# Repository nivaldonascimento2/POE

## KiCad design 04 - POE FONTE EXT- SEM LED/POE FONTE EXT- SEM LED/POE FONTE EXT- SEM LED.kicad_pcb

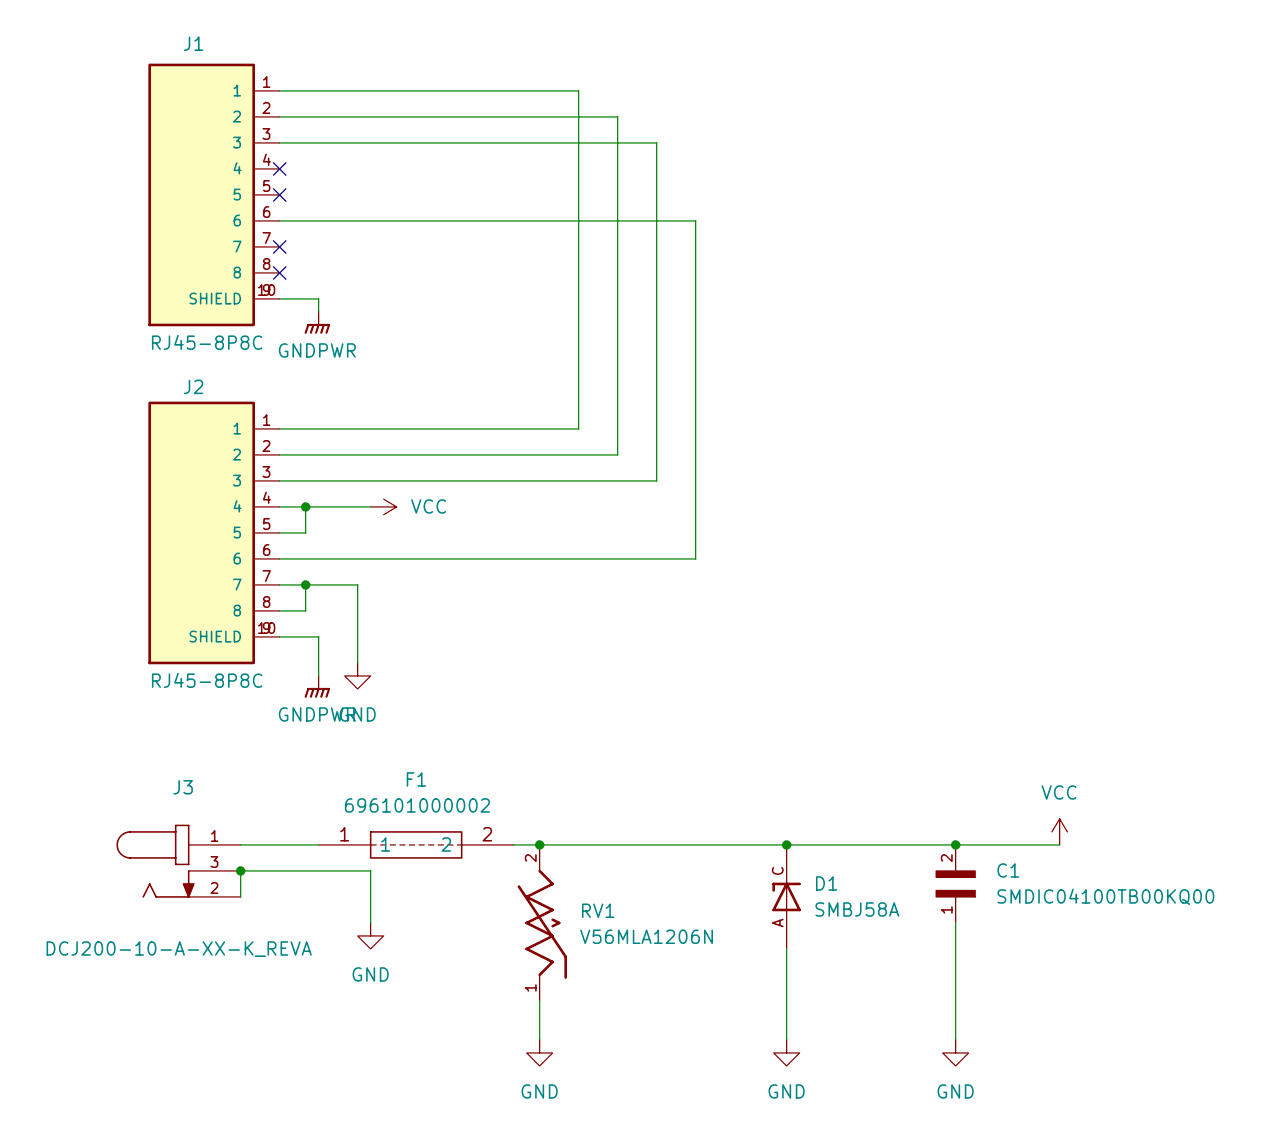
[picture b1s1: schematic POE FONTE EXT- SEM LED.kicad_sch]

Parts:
C1: SMDIC04100TB00KQ00; CAP_SMDIC04100TB00KQ00; PARTREV 04.23
D1: SMBJ58A; DIOM4336X265N; PARTREV F2102
F1: 696101000002; Mouser Part Number 710-696101000002
J1, J2: RJ45-8P8C
J3: DCJ200-10-A-XX-K_REVA; GCT_DCJ200-10-A-XX-K_REVA; PARTREV A
RV1: V56MLA1206N; VARC3216X180N

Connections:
GND: C1.1, D1.A, J2.7, J2.8, J3.2, J3.3, RV1.1
GNDPWR: J1.9 (SHIELD), J1.10 (SHIELD), J2.9 (SHIELD), J2.10 (SHIELD)
unnamed: F1.1, J3.1
unnamed: J1.1, J2.1
unnamed: J1.2, J2.2
unnamed: J1.3, J2.3
unnamed: J1.6, J2.6
VCC: C1.2, D1.C, F1.2, J2.4, J2.5, RV1.2

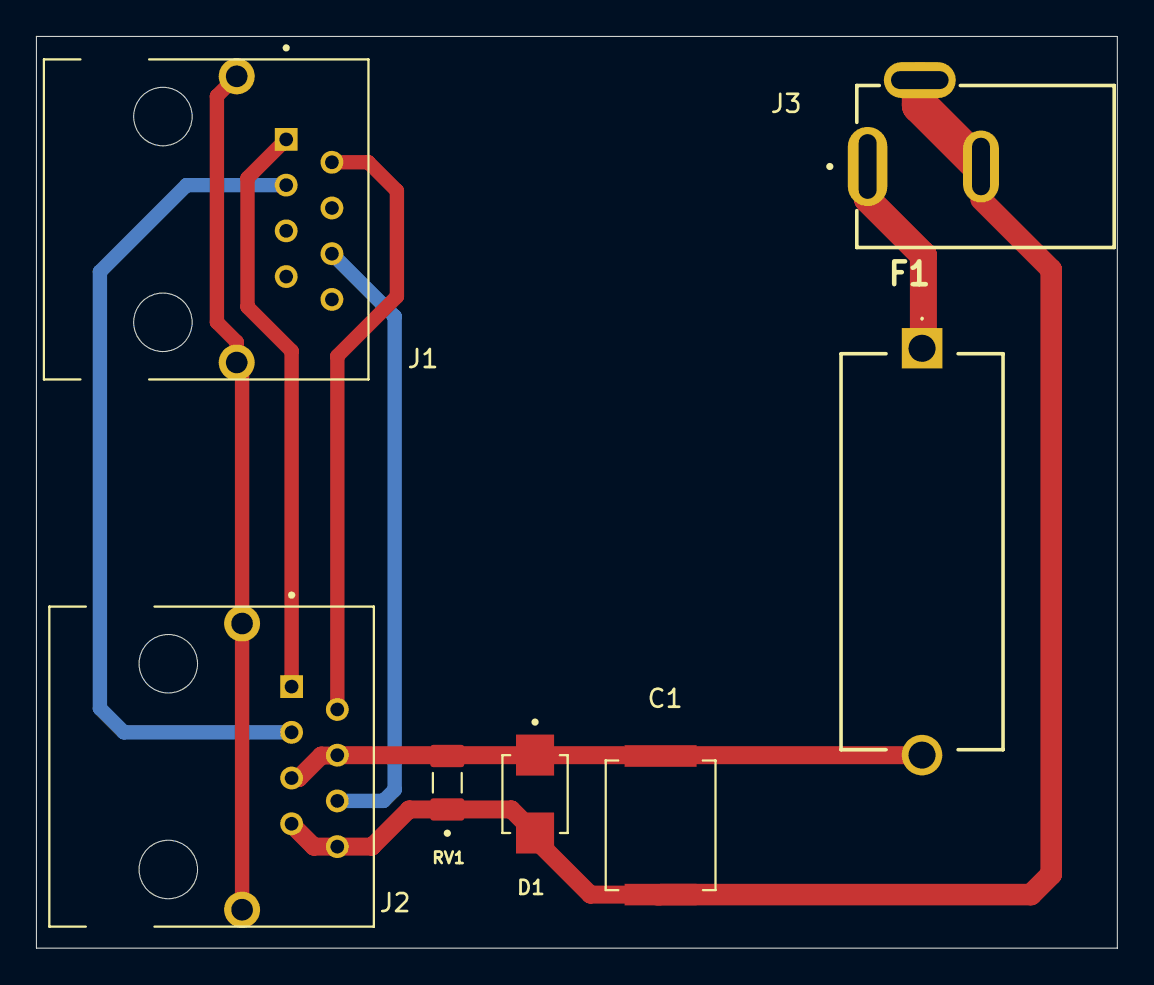
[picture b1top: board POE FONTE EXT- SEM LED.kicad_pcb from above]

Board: 2 copper layers, 60.0 x 50.6 mm, 7 parts (0 on the bottom side), 8 nets.

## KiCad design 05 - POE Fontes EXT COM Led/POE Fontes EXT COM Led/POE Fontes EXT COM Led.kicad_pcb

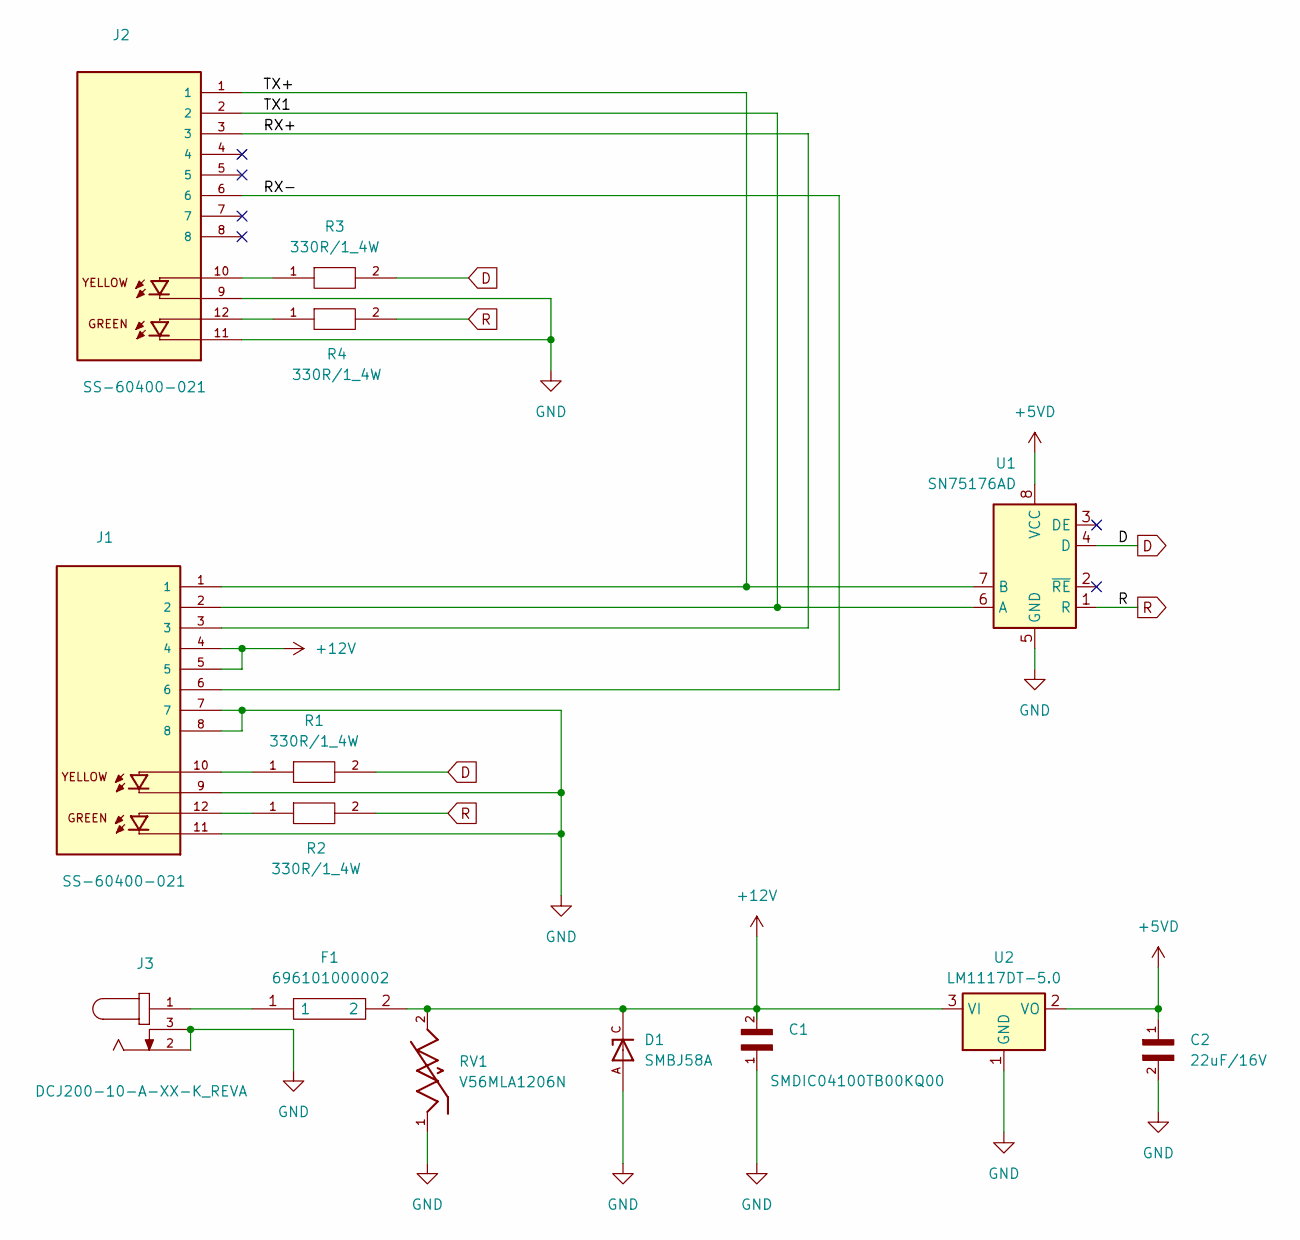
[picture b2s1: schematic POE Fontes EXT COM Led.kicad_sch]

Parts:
C1: SMDIC04100TB00KQ00; CAP_SMDIC04100TB00KQ00; PARTREV 04.23
C2: 22uF/16V; 22uF_16V
D1: SMBJ58A; DIOM4336X265N; PARTREV F2102
F1: 696101000002; Mouser Part Number 710-696101000002
J1, J2: SS-60400-021; BEL_SS-60400-021; PARTREV A0
J3: DCJ200-10-A-XX-K_REVA; GCT_DCJ200-10-A-XX-K_REVA; PARTREV A
R1, R2, R3, R4: 330R/1_4W; RESC2012X65N
RV1: V56MLA1206N; VARC3216X180N
U1: SN75176AD; SOIC-8_3.9x4.9mm_P1.27mm
U2: LM1117DT-5.0; TO-252-3_TabPin2

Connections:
+5VD: C2.1, U1.8 (VCC), U2.2 (VO)
+12V: C1.2, D1.C, F1.2, J1.4, J1.5, RV1.2, U2.3 (VI)
/RX+: J1.3, J2.3
/RX-: J1.6, J2.6
/TX1: J1.2, J2.2, U1.6 (A)
/TX+: J1.1, J2.1, U1.7 (B)
D: R1.2, R3.2, U1.4 (D)
GND: C1.1, C2.2, D1.A, J1.7, J1.8, J1.9, J1.11, J2.9, J2.11, J3.2, J3.3, RV1.1, U1.5 (GND), U2.1 (GND)
unnamed: F1.1, J3.1
unnamed: J1.10, R1.1
unnamed: J1.12, R2.1
unnamed: J2.10, R3.1
unnamed: J2.12, R4.1
R: R2.2, R4.2, U1.1 (R)

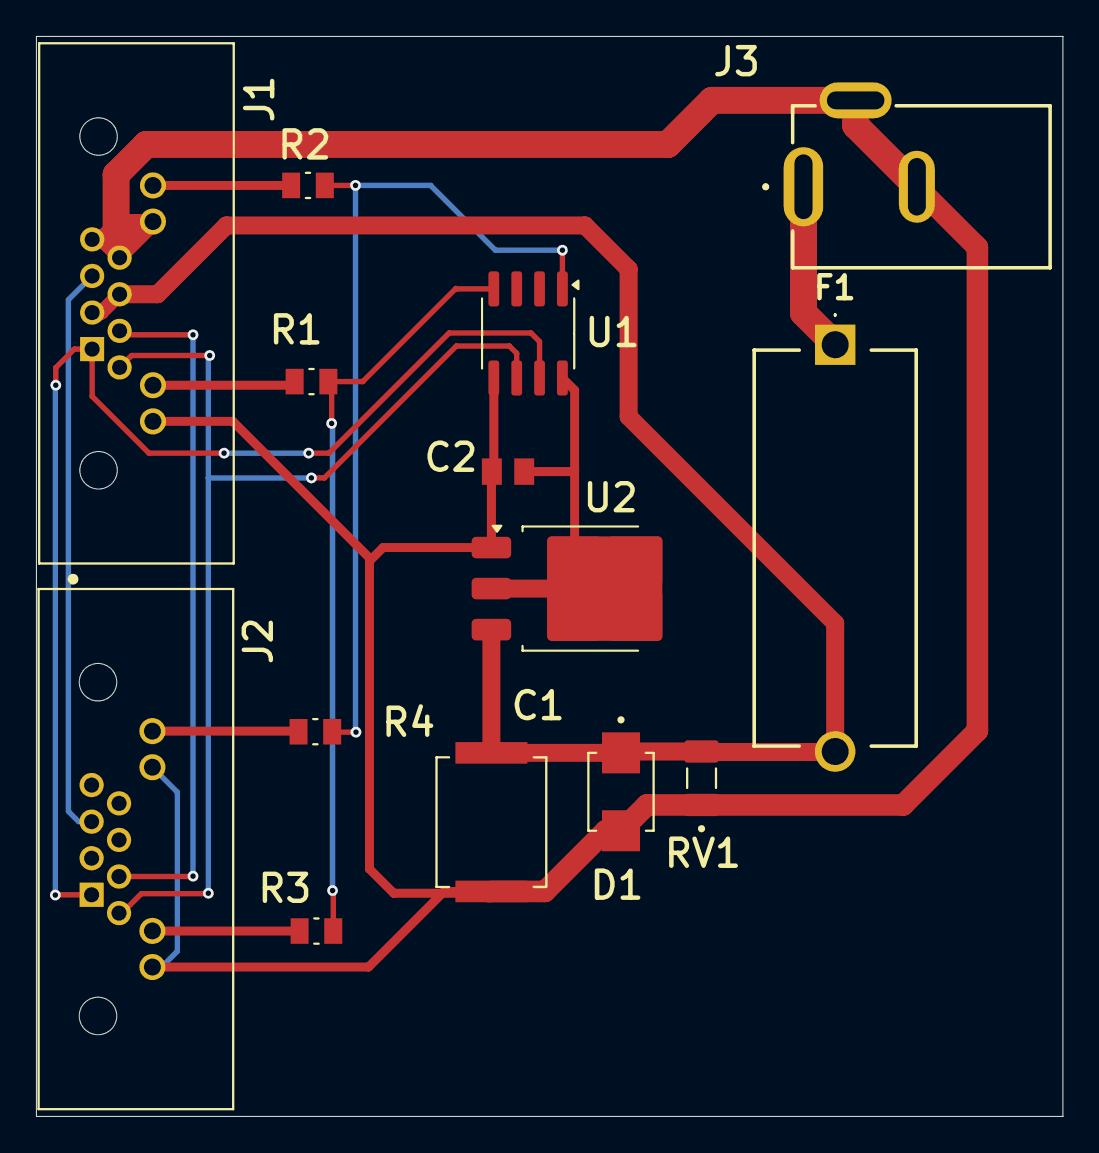
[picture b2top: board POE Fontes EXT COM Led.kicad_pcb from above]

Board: 2 copper layers, 57.0 x 60.0 mm, 14 parts (0 on the bottom side), 14 nets.

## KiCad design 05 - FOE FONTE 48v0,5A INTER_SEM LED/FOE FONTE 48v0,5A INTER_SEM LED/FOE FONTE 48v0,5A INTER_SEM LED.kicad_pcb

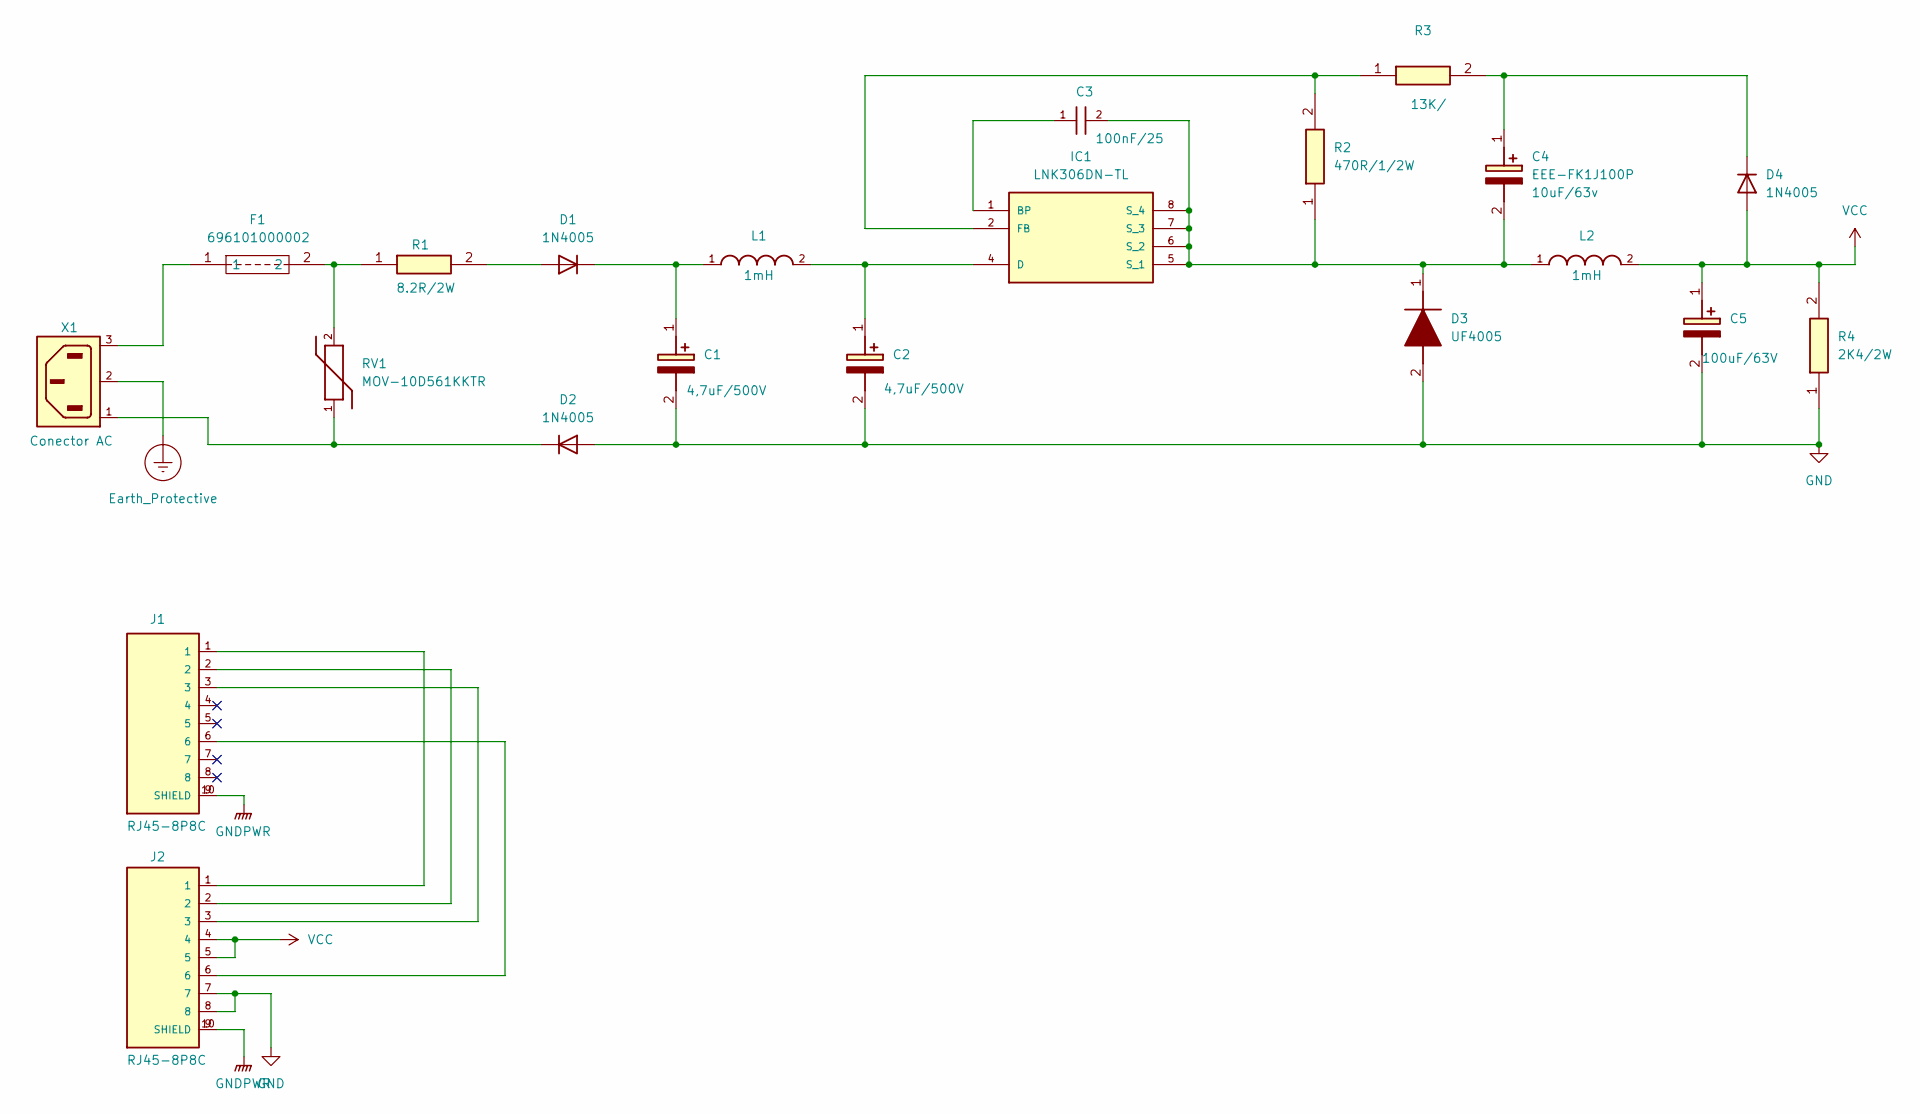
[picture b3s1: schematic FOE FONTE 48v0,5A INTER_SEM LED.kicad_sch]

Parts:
C1, C2: ULT2H4R7MNL1GS; CAPAE1030X1450N; Mouser Part Number 647-ULT2H4R7MNL1GS
C3: 100nF/25; WCAP-CSGP_0603_W
C4: EEE-FK1J100P; EEE1AA101SP; Mouser Part Number 667-EEE-FK1J100P
C5: MAL215097803E3; CAPAE1050X1430N; Mouser Part Number 594-MAL215097803E3
D1, D2, D4: 1N4005; D_DO-41_SOD81_P10.16mm_Horizontal
D3: UF4005; DIOAD1510W84L490D255; Mouser Part Number 637-UF4005
F1: 696101000002; Mouser Part Number 710-696101000002
IC1: LNK306DN-TL; SOIC127P600X175-7N; MOUSER_PART_NUMBER 869-LNK306DN-TL
J1, J2: RJ45-8P8C
L1, L2: WE-PD2HV_1054
R1: CRGH2512J8R2; RESC6432X65N; Mouser Part Number 279-CRGH2512J8R2
R2: RCC1206470RFKEA; RCC1206_e3; Mouser Part Number 71-RCC1206470RFKEA
R3: ERA-6ARB133V; ERA6AEB1020V; Mouser Part Number 667-ERA-6ARB133V
R4: 2K4/2W; RESC6432X65N; Mouser Part Number 279-35212K4FT
RV1: MOV-10D561KKTR; MOV10D511K; MOUSER_PART_NUMBER 652-MOV-10D511K
X1: Conector AC; 6ESRM-P; MPN 6ESRM-P

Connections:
Earth_Protective: X1.2
GND: C1.2 (-), C2.2 (-), C5.2 (-), D2.2 (A), D3.2 (A), J2.7, J2.8, R4.1
GNDPWR: J1.9 (SHIELD), J1.10 (SHIELD), J2.9 (SHIELD), J2.10 (SHIELD)
unnamed: C1.1 (+), D1.1 (K), L1.1
unnamed: C2.1 (+), IC1.4 (D), L1.2
unnamed: C4.1 (+), D4.1 (K), R3.2
unnamed: C3.2, C4.2 (-), D3.1 (K), IC1.5 (S_1), IC1.6 (S_2), IC1.7 (S_3), IC1.8 (S_4), L2.1, R2.1
unnamed: D1.2 (A), R1.2
unnamed: D2.1 (K), RV1.1, X1.1
unnamed: F1.1, X1.3
unnamed: F1.2, R1.1, RV1.2
unnamed: C3.1, IC1.1 (BP)
unnamed: IC1.2 (FB), R2.2, R3.1
unnamed: J1.1, J2.1
unnamed: J1.2, J2.2
unnamed: J1.3, J2.3
unnamed: J1.6, J2.6
VCC: C5.1 (+), D4.2 (A), J2.4, J2.5, L2.2, R4.2

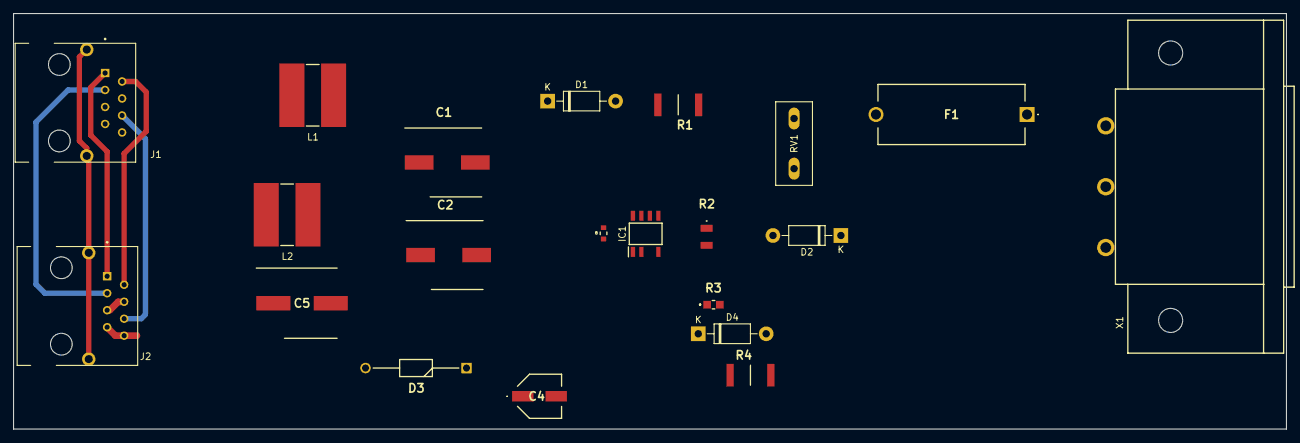
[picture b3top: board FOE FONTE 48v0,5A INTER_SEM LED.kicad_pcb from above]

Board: 2 copper layers, 190.4 x 62.2 mm, 21 parts (0 on the bottom side), 17 nets.

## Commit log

2024-09-12 POE
    Subindo projeto POE
2024-09-16 Subindo Projeto POE
2024-10-17 Create Diagrama de teste.dft
    backup projeto
